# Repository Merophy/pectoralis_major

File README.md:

# pectoralis_major
The pectoralis is a large muscle that attaches to the humerus of the wing at the deltopectoral crest.

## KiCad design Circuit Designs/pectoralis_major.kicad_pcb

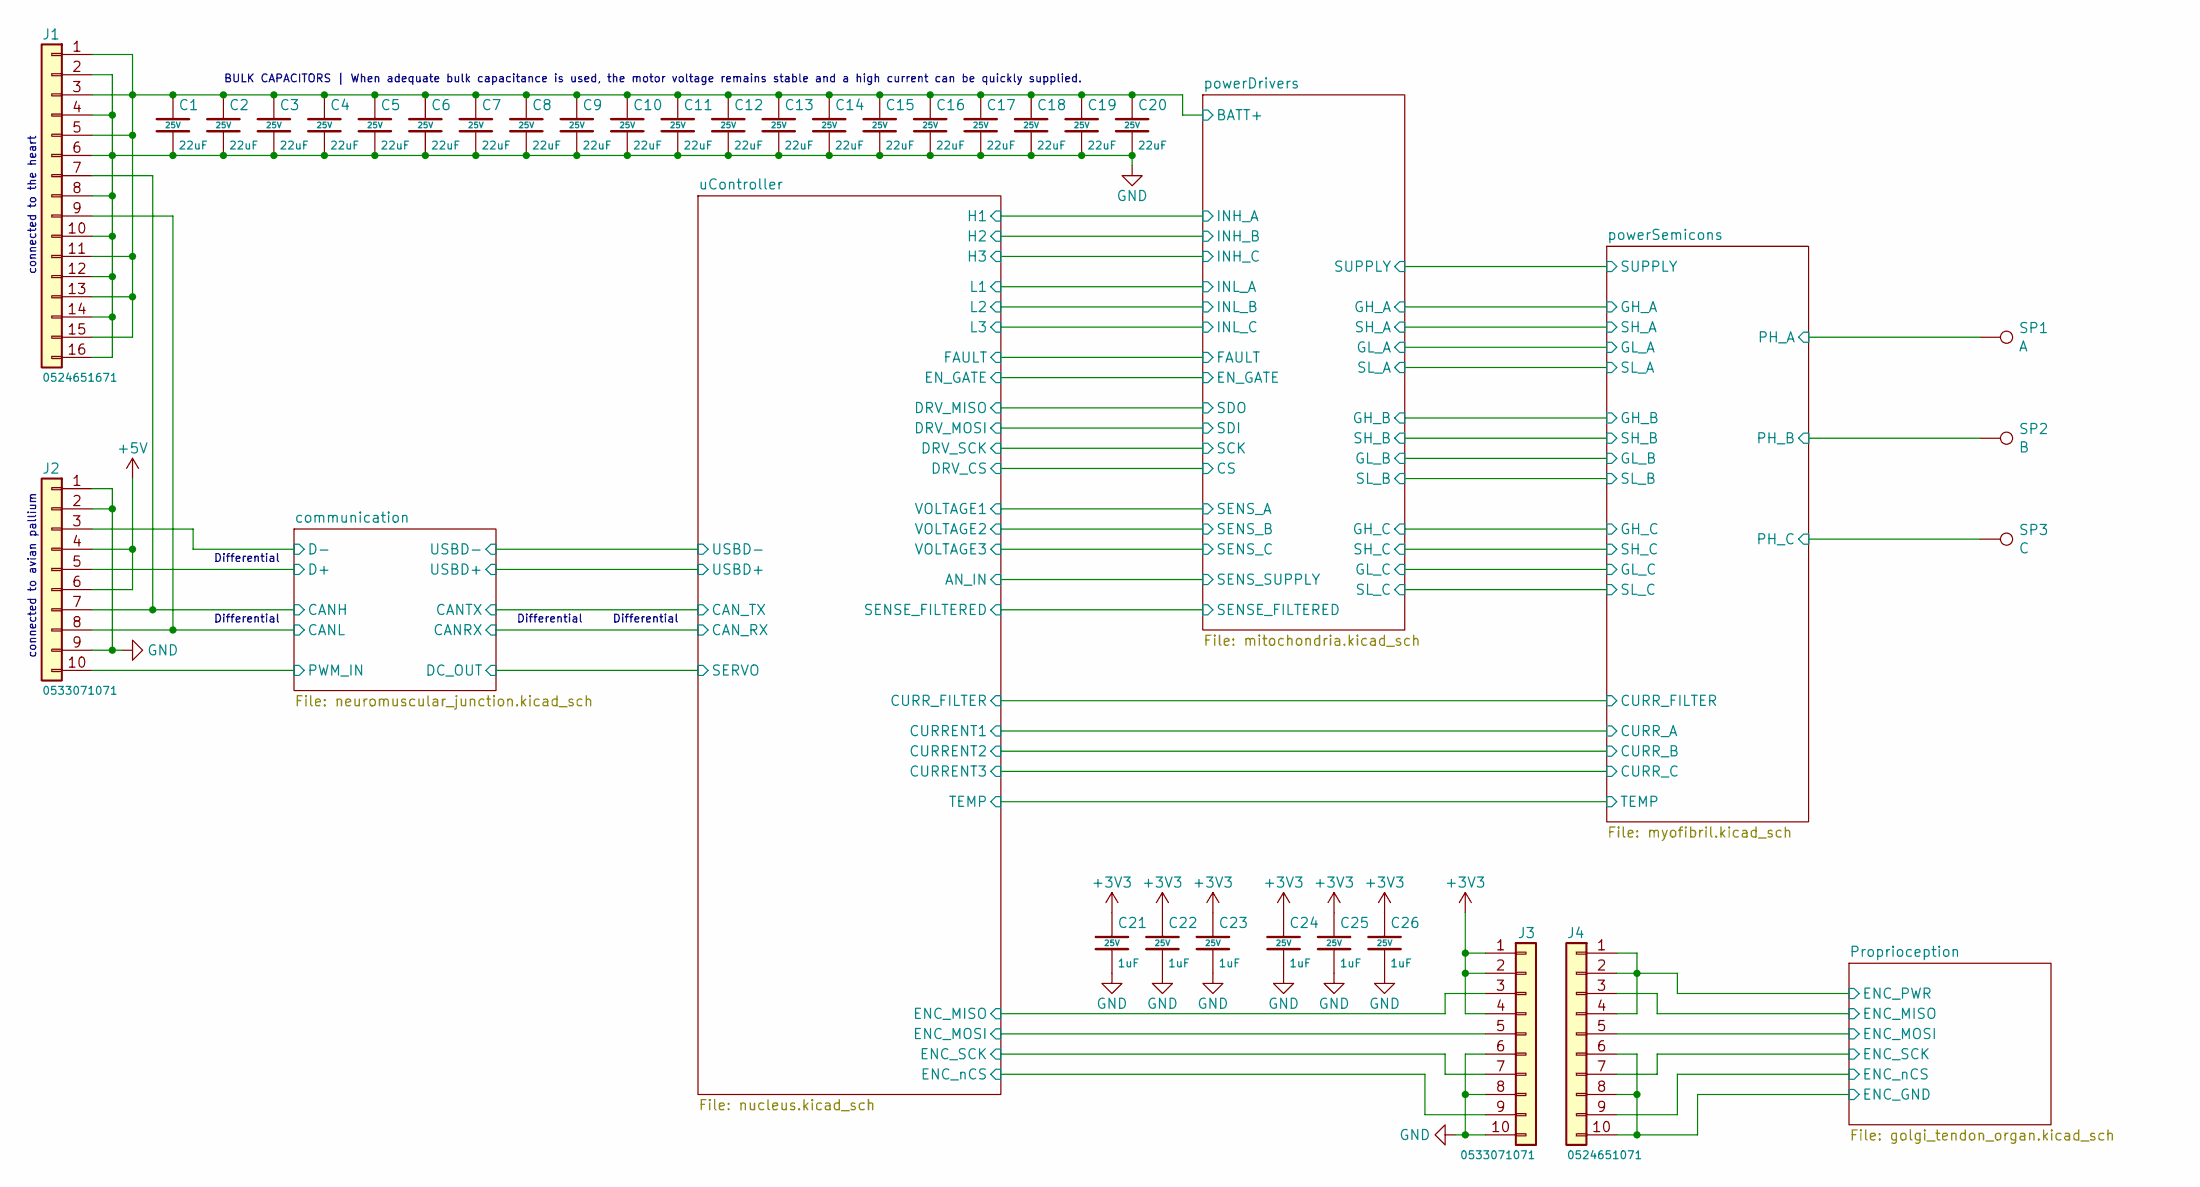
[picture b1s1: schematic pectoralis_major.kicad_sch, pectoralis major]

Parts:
C1, C2, C3, C4, C5, C6, C7, C8, C9, C10, C11, C12, C13, C14, C15, C16, C17, C18, C19, C20: 22uF; C-0805; Voltage 25V; MFR. Part # CL21A226MAQNNNE; JLCPCB Part # C45783
C21, C22, C23, C24, C25, C26: 1uF; C-0402; Voltage 25V; MFR. Part # CL05A105KA5NQNC; JLCPCB Part # C52923
J1: 0524651671; 524651671; MFR Part # 0524651671; Digikey Part # WM7089CT-ND
J2, J3: 0533071071; MFR Part # 0533071071; Digikey Part # WM8918CT-ND
J4: 0524651071; 524651071; MFR Part # 0524651071; Farnell Part # 2063791
SP1: A; SolderPt_2.5x4mm
SP2: B; SolderPt_2.5x4mm
SP3: C; SolderPt_2.5x4mm

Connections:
+3V3: C21.1, C22.1, C23.1, C24.1, C25.1, C26.1, J3.1, J3.2, J3.4; also elsewhere on the board
+5V: J2.4, J2.6; also elsewhere on the board
/Proprioception/ENC_GND: J4.6, J4.8, J4.10; also elsewhere on the board
/Proprioception/ENC_MISO: J4.3; also elsewhere on the board
/Proprioception/ENC_MOSI: J4.5; also elsewhere on the board
/Proprioception/ENC_PWR: J4.1, J4.2, J4.4; also elsewhere on the board
/Proprioception/ENC_SCK: J4.7; also elsewhere on the board
/Proprioception/ENC_nCS: J4.9; also elsewhere on the board
/communication/CANH: J1.7, J2.7; also elsewhere on the board
/communication/CANL: J1.9, J2.8; also elsewhere on the board
/communication/D+: J2.5; also elsewhere on the board
/communication/D-: J2.3; also elsewhere on the board
/communication/PWM_IN: J2.10; also elsewhere on the board
/powerSemicons/PH_A: SP1.1; also elsewhere on the board
/powerSemicons/PH_B: SP2.1; also elsewhere on the board
/powerSemicons/PH_C: SP3.1; also elsewhere on the board
/uController/ENC_MISO: J3.3; also elsewhere on the board
/uController/ENC_MOSI: J3.5; also elsewhere on the board
/uController/ENC_SCK: J3.7; also elsewhere on the board
/uController/ENC_nCS: J3.9; also elsewhere on the board
GND: C1.2, C2.2, C3.2, C4.2, C5.2, C6.2, C7.2, C8.2, C9.2, C10.2, C11.2, C12.2, C13.2, C14.2, C15.2, C16.2, C17.2, C18.2, C19.2, C20.2, C21.2, C22.2, C23.2, C24.2, C25.2, C26.2, J1.2, J1.4, J1.6, J1.8, J1.10, J1.12, J1.14, J1.16, J2.1, J2.2, J2.9, J3.6, J3.8, J3.10; also elsewhere on the board
PVDD2: C1.1, C2.1, C3.1, C4.1, C5.1, C6.1, C7.1, C8.1, C9.1, C10.1, C11.1, C12.1, C13.1, C14.1, C15.1, C16.1, C17.1, C18.1, C19.1, C20.1, J1.1, J1.3, J1.5, J1.11, J1.13, J1.15; also elsewhere on the board

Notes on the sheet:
Differential
BULK CAPACITORS | When adequate bulk capacitance is used, the motor voltage remains stable and a high current can be quickly supplied.
connected to avian pallium
connected to the heart

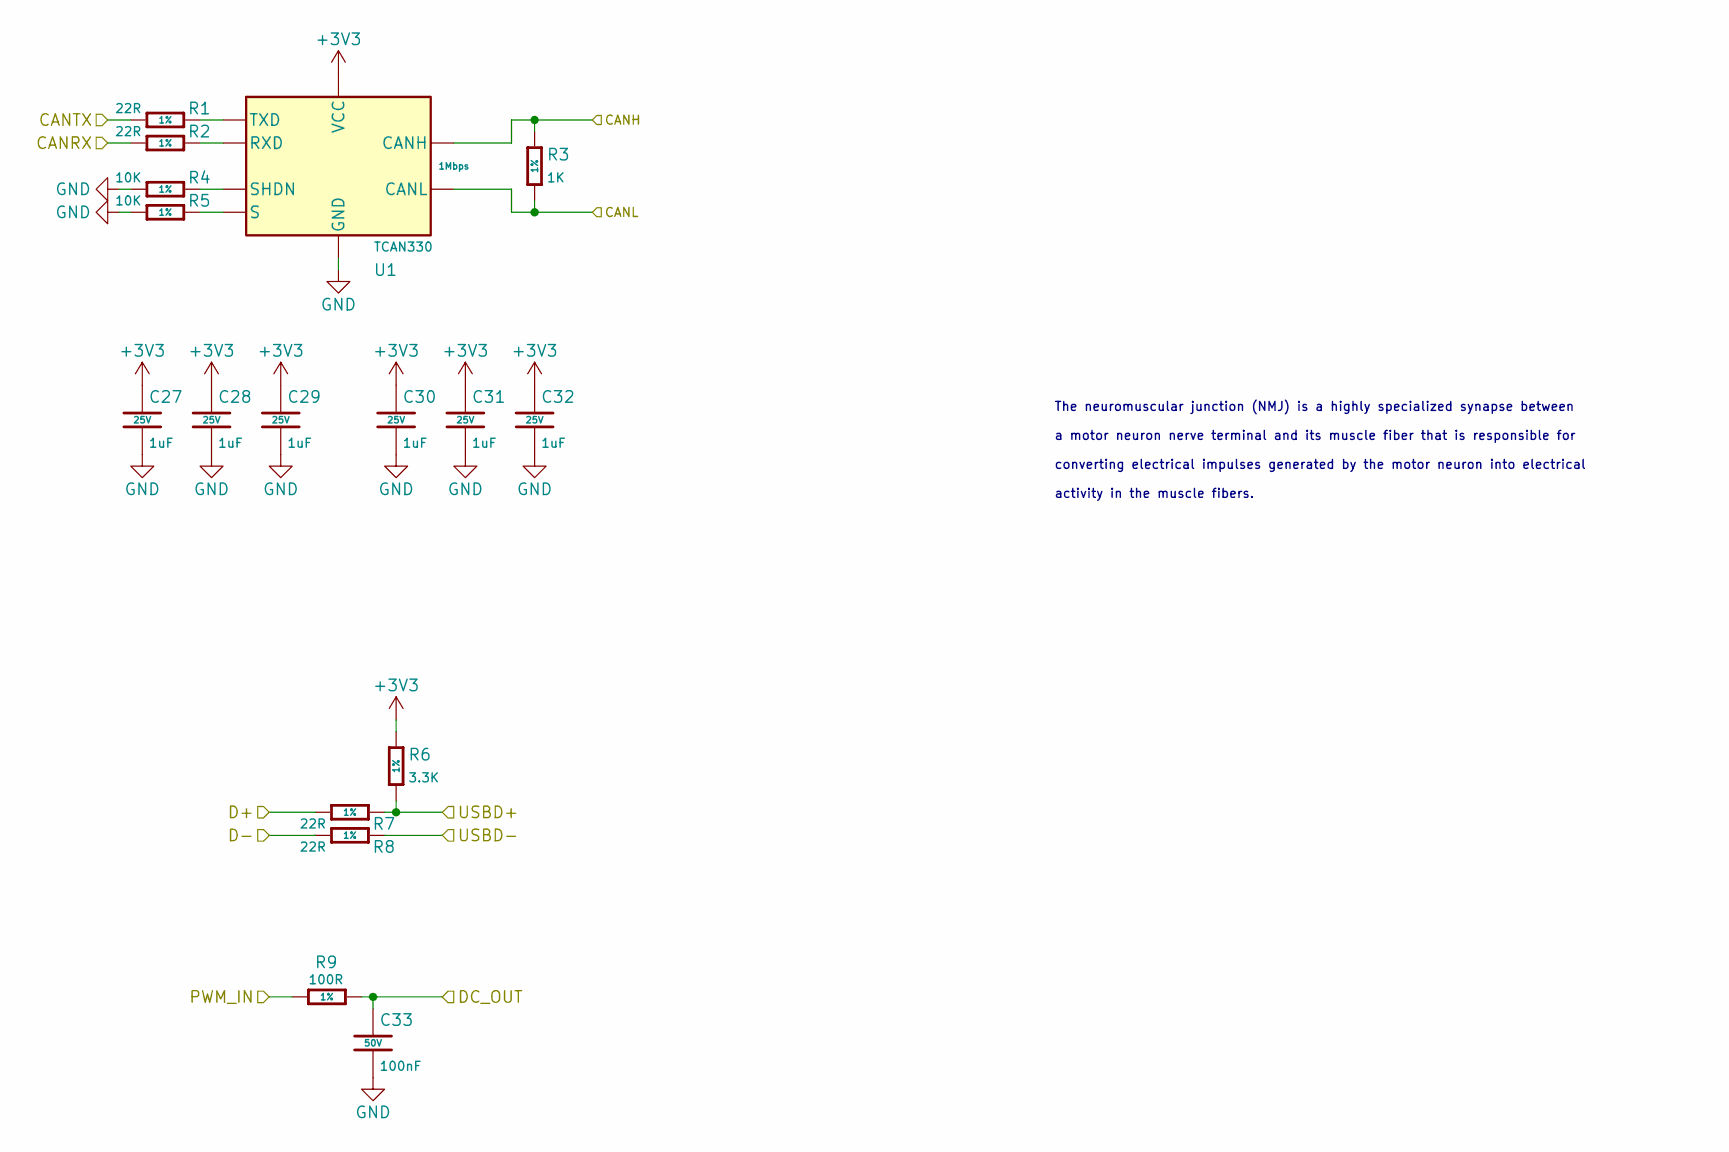
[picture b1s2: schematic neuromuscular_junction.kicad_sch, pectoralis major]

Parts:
C27, C28, C29, C30, C31, C32: 1uF; C-0402; Voltage 25V; MFR. Part # CL05A105KA5NQNC; JLCPCB Part # C52923
C33: 100nF; C-0402; Voltage 50V; MFR. Part # CL05B104KB54PNC; JLCPCB Part # C307331
R1, R2, R7, R8: 22R; R-0402; Tolerance 1%; MFR. Part # 0402WGF220JTCE; JLCPCB Part # C25092
R3: 1K; R-0402; Tolerance 1%; MFR. Part # 0402WGF1001TCE; JLCPCB Part # C11702
R4, R5: 10K; R-0402; Tolerance 1%; MFR. Part # 0402WGF1002TCE; JLCPCB Part # C25744
R6: 3.3K; R-0402; Tolerance 1%; MFR. Part # 0402WGF3301TCE; JLCPCB Part # C25890
R9: 100R; R-0402; Tolerance 1%; MFR. Part # 0402WGF1000TCE; JLCPCB Part # C25076
U1: TCAN330; TSOT-23-8; MFR. Part # TCAN330GDCNR; Digikey Part # 296-TCAN330GDCNRCT-ND

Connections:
+3V3: C27.1, C28.1, C29.1, C30.1, C31.1, C32.1, R6.1, U1.3 (VCC); also elsewhere on the board
/communication/CANH: R3.1, U1.7 (CANH); also elsewhere on the board
/communication/CANL: R3.2, U1.6 (CANL); also elsewhere on the board
/communication/CANRX: R2.1; also elsewhere on the board
/communication/CANTX: R1.1; also elsewhere on the board
/communication/D+: R7.1; also elsewhere on the board
/communication/D-: R8.1; also elsewhere on the board
/communication/DC_OUT: C33.1, R9.2; also elsewhere on the board
/communication/PWM_IN: R9.1; also elsewhere on the board
/communication/USBD+: R6.2, R7.2; also elsewhere on the board
/communication/USBD-: R8.2; also elsewhere on the board
GND: C27.2, C28.2, C29.2, C30.2, C31.2, C32.2, C33.2, R4.1, R5.1, U1.2 (GND); also elsewhere on the board
unnamed: R1.2, U1.1 (TXD)
unnamed: R2.2, U1.4 (RXD)
unnamed: R4.2, U1.5 (SHDN)
unnamed: R5.2, U1.8 (S)

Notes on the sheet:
The neuromuscular junction (NMJ) is a highly specialized synapse between a motor neuron nerve terminal and its muscle fiber that is responsible for converting electrical impulses generated by the motor neuron into electrical activity in the muscle fibers.

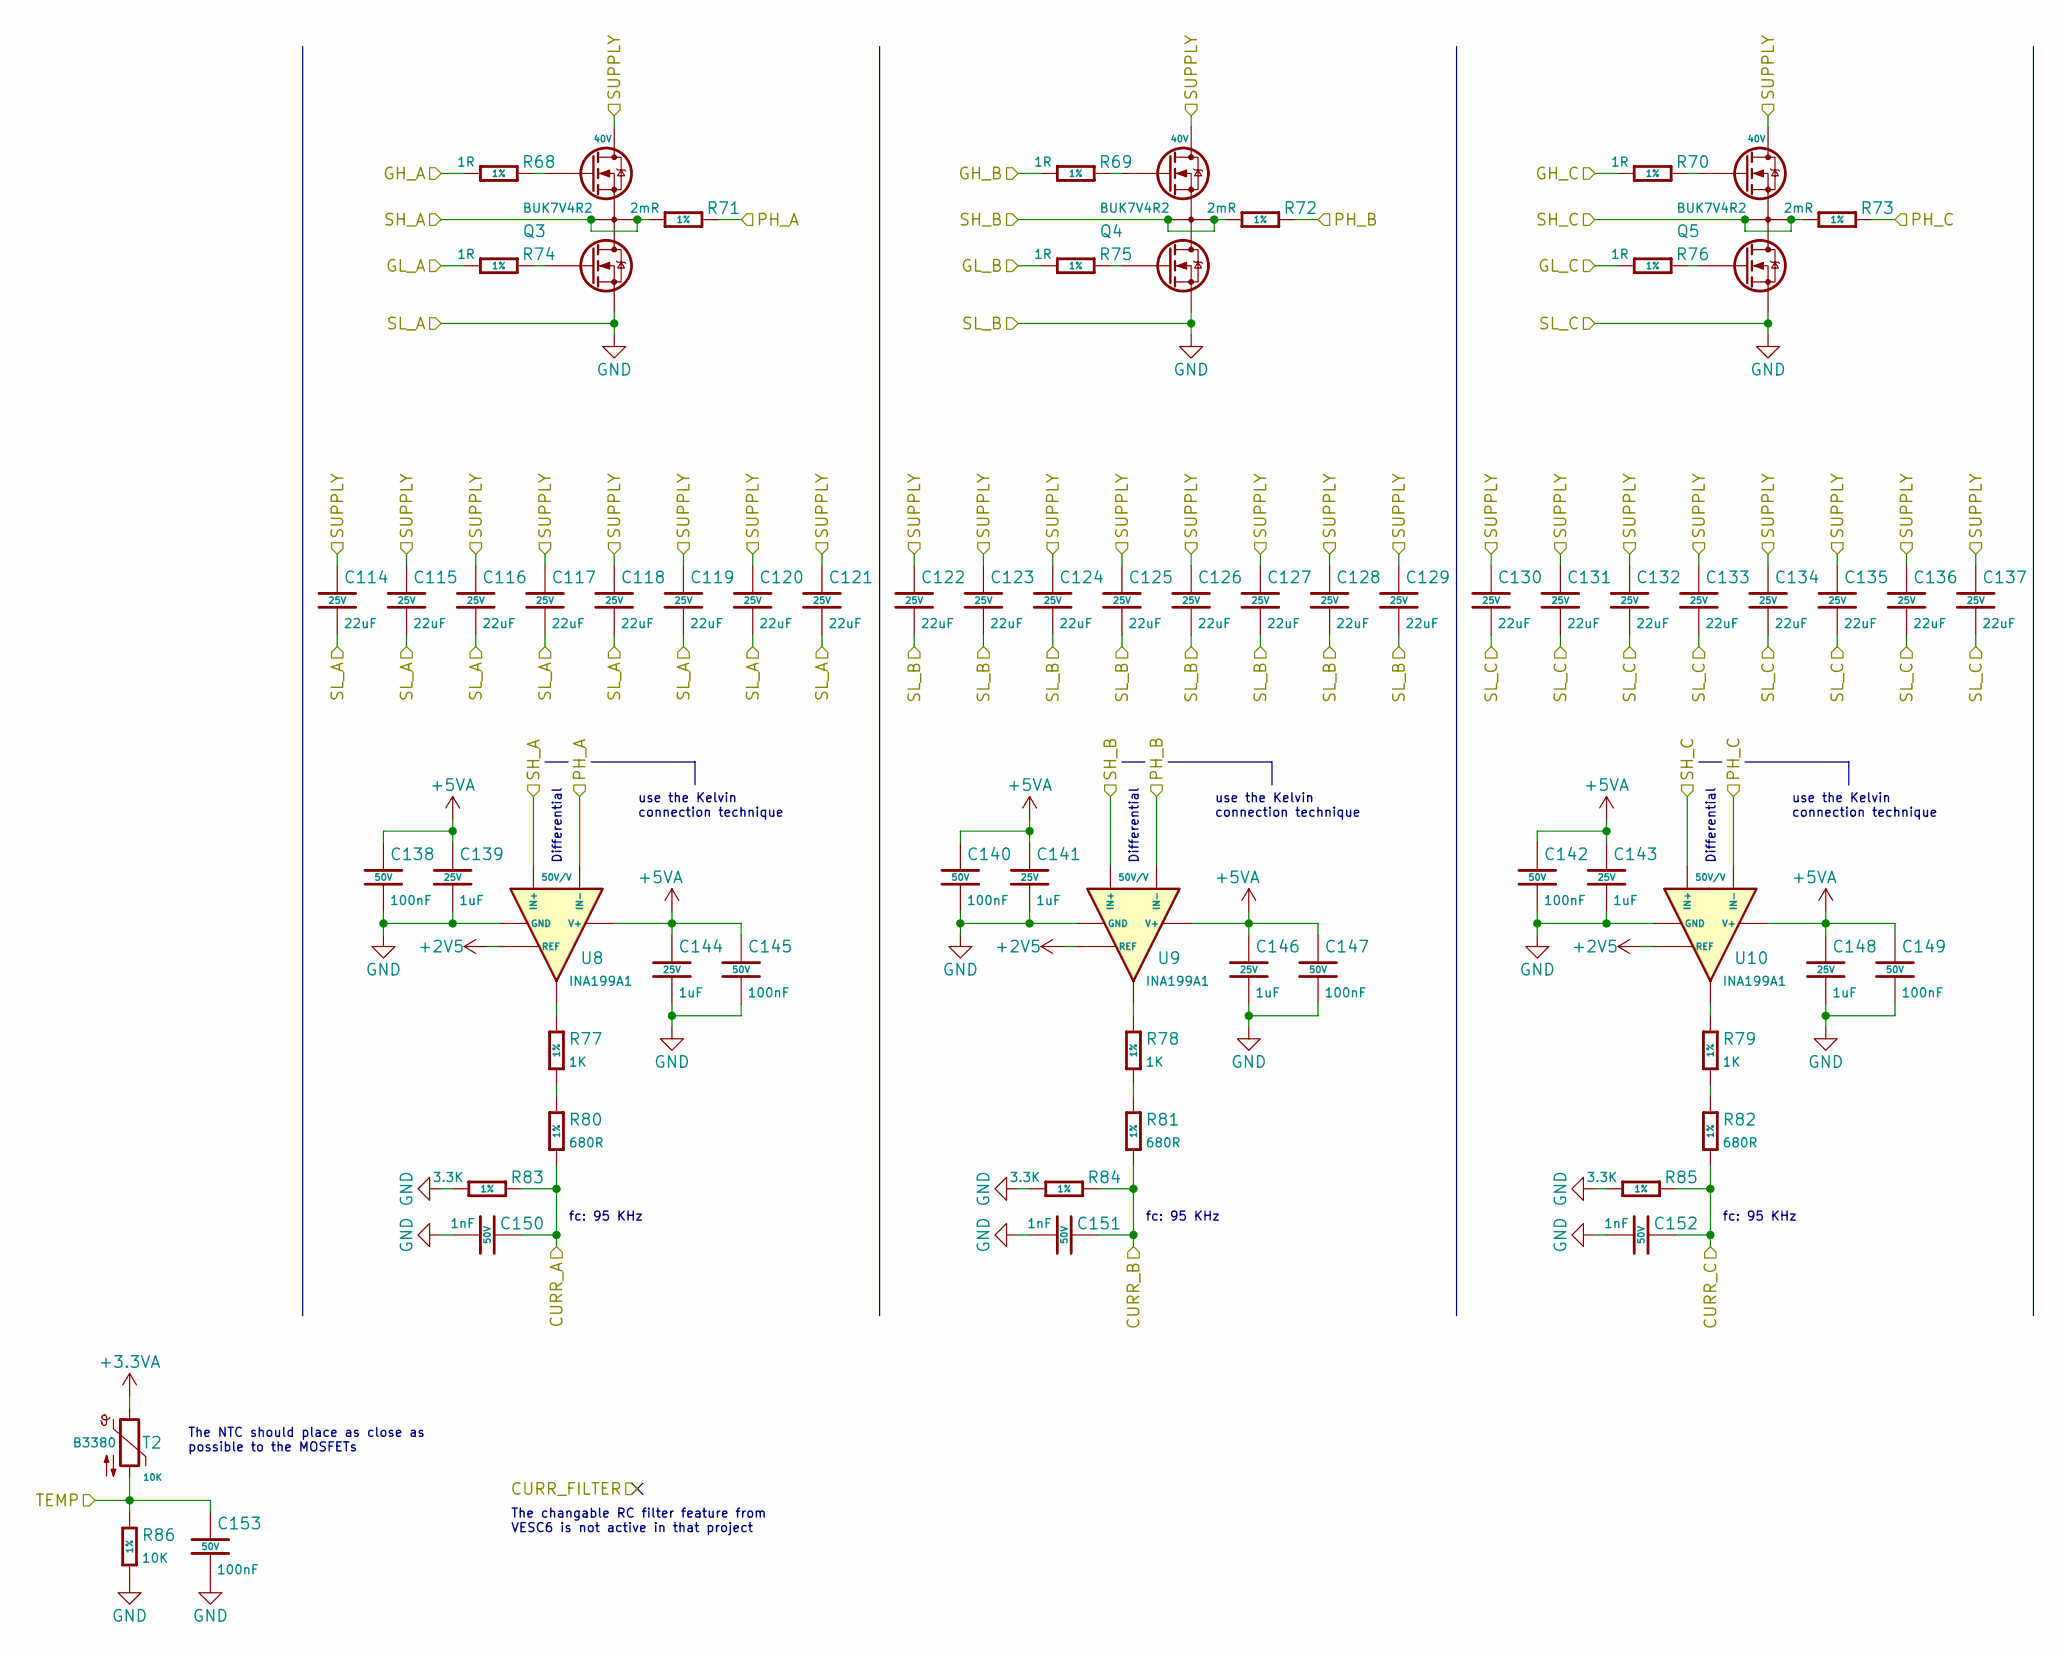
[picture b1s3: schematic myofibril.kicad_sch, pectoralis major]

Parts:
C114, C115, C116, C117, C118, C119, C120, C121, C122, C123, C124, C125, C126, C127, C128, C129, C130, C131, C132, C133, C134, C135, C136, C137: 22uF; C-0805; Voltage 25V; MFR. Part # CL21A226MAQNNNE; JLCPCB Part # C45783
C138, C140, C142, C145, C147, C149, C153: 100nF; C-0402; Voltage 50V; MFR. Part # CL05B104KB54PNC; JLCPCB Part # C307331
C139, C141, C143, C144, C146, C148: 1uF; C-0402; Voltage 25V; MFR. Part # CL05A105KA5NQNC; JLCPCB Part # C52923
C150, C151, C152: 1nF; C-0402; Voltage 50V; MFR. Part # 0402B102K500NT; JLCPCB Part # C1523
Q3, Q4, Q5: BUK7V4R2; SOT-1205; MFR. Part # BUK7V4R2; Digikey Part # 1727-BUK7V4R2-40HXCT-ND
R68, R69, R70, R74, R75, R76: 1R; R-0402; Tolerance 1%; MFR. Part # 0402WGF100KTCE; JLCPCB Part # C25086
R71, R72, R73: 2mR; R-1206; Tolerance 1%; MFR. Part # PA1206FRM470R002L; JLCPCB Part # C728295
R77, R78, R79: 1K; R-0402; Tolerance 1%; MFR. Part # 0402WGF1001TCE; JLCPCB Part # C11702
R80, R81, R82: 680R; R-0402; Tolerance 1%; MFR. Part # 0402WGF6800TCE; JLCPCB Part # C25130
R83, R84, R85: 3.3K; R-0402; Tolerance 1%; MFR. Part # 0402WGF3301TCE; JLCPCB Part # C25890
R86: 10K; R-0402; Tolerance 1%; MFR. Part # 0402WGF1002TCE; JLCPCB Part # C25744
T2: B3380; R-0402; MFR. Part # NCP15XH103F03RC; JLCPCB Part # C77131
U8, U9, U10: INA199A1; SOT-363; MFR. Part # INA199A1DCKR; JLCPCB Part # C59135

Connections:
+2V5: U8.1 (REF), U9.1 (REF), U10.1 (REF); also elsewhere on the board
+3.3VA: T2.1; also elsewhere on the board
+5VA: C138.1, C139.1, C140.1, C141.1, C142.1, C143.1, C144.1, C145.1, C146.1, C147.1, C148.1, C149.1, U8.3 (V+), U9.3 (V+), U10.3 (V+); also elsewhere on the board
/powerDrivers/GH_A: R68.1; also elsewhere on the board
/powerDrivers/GH_B: R69.1; also elsewhere on the board
/powerDrivers/GH_C: R70.1; also elsewhere on the board
/powerDrivers/GL_A: R74.1; also elsewhere on the board
/powerDrivers/GL_B: R75.1; also elsewhere on the board
/powerDrivers/GL_C: R76.1; also elsewhere on the board
/powerDrivers/SH_A: Q3.3 (S1), Q3.6 (S1/D2), R71.1, U8.4 (IN+); also elsewhere on the board
/powerDrivers/SH_B: Q4.3 (S1), Q4.6 (S1/D2), R72.1, U9.4 (IN+); also elsewhere on the board
/powerDrivers/SH_C: Q5.3 (S1), Q5.6 (S1/D2), R73.1, U10.4 (IN+); also elsewhere on the board
/powerSemicons/CURR_A: C150.2, R80.2, R83.2; also elsewhere on the board
/powerSemicons/CURR_B: C151.2, R81.2, R84.2; also elsewhere on the board
/powerSemicons/CURR_C: C152.2, R82.2, R85.2; also elsewhere on the board
/powerSemicons/PH_A: R71.2, U8.5 (IN-); also elsewhere on the board
/powerSemicons/PH_B: R72.2, U9.5 (IN-); also elsewhere on the board
/powerSemicons/PH_C: R73.2, U10.5 (IN-); also elsewhere on the board
/powerSemicons/TEMP: C153.1, R86.1, T2.2; also elsewhere on the board
GND: C114.2, C115.2, C116.2, C117.2, C118.2, C119.2, C120.2, C121.2, C122.2, C123.2, C124.2, C125.2, C126.2, C127.2, C128.2, C129.2, C130.2, C131.2, C132.2, C133.2, C134.2, C135.2, C136.2, C137.2, C138.2, C139.2, C140.2, C141.2, C142.2, C143.2, C144.2, C145.2, C146.2, C147.2, C148.2, C149.2, C150.1, C151.1, C152.1, C153.2, Q3.1 (S2), Q4.1 (S2), Q5.1 (S2), R83.1, R84.1, R85.1, R86.2, U8.2 (GND), U9.2 (GND), U10.2 (GND); also elsewhere on the board
unnamed: Q3.2 (G2), R74.2
unnamed: Q3.4 (G1), R68.2
unnamed: Q4.2 (G2), R75.2
unnamed: Q4.4 (G1), R69.2
unnamed: Q5.2 (G2), R76.2
unnamed: Q5.4 (G1), R70.2
unnamed: R77.1, U8.6
unnamed: R77.2, R80.1
unnamed: R78.1, U9.6
unnamed: R78.2, R81.1
unnamed: R79.1, U10.6
unnamed: R79.2, R82.1
PVDD2: C114.1, C115.1, C116.1, C117.1, C118.1, C119.1, C120.1, C121.1, C122.1, C123.1, C124.1, C125.1, C126.1, C127.1, C128.1, C129.1, C130.1, C131.1, C132.1, C133.1, C134.1, C135.1, C136.1, C137.1, Q3.5 (D1), Q4.5 (D1), Q5.5 (D1); also elsewhere on the board

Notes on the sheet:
Differential
The changable RC filter feature from VESC6 is not active in that project
use the Kelvin connection technique
fc: 95 KHz
The NTC should place as close as possible to the MOSFETs

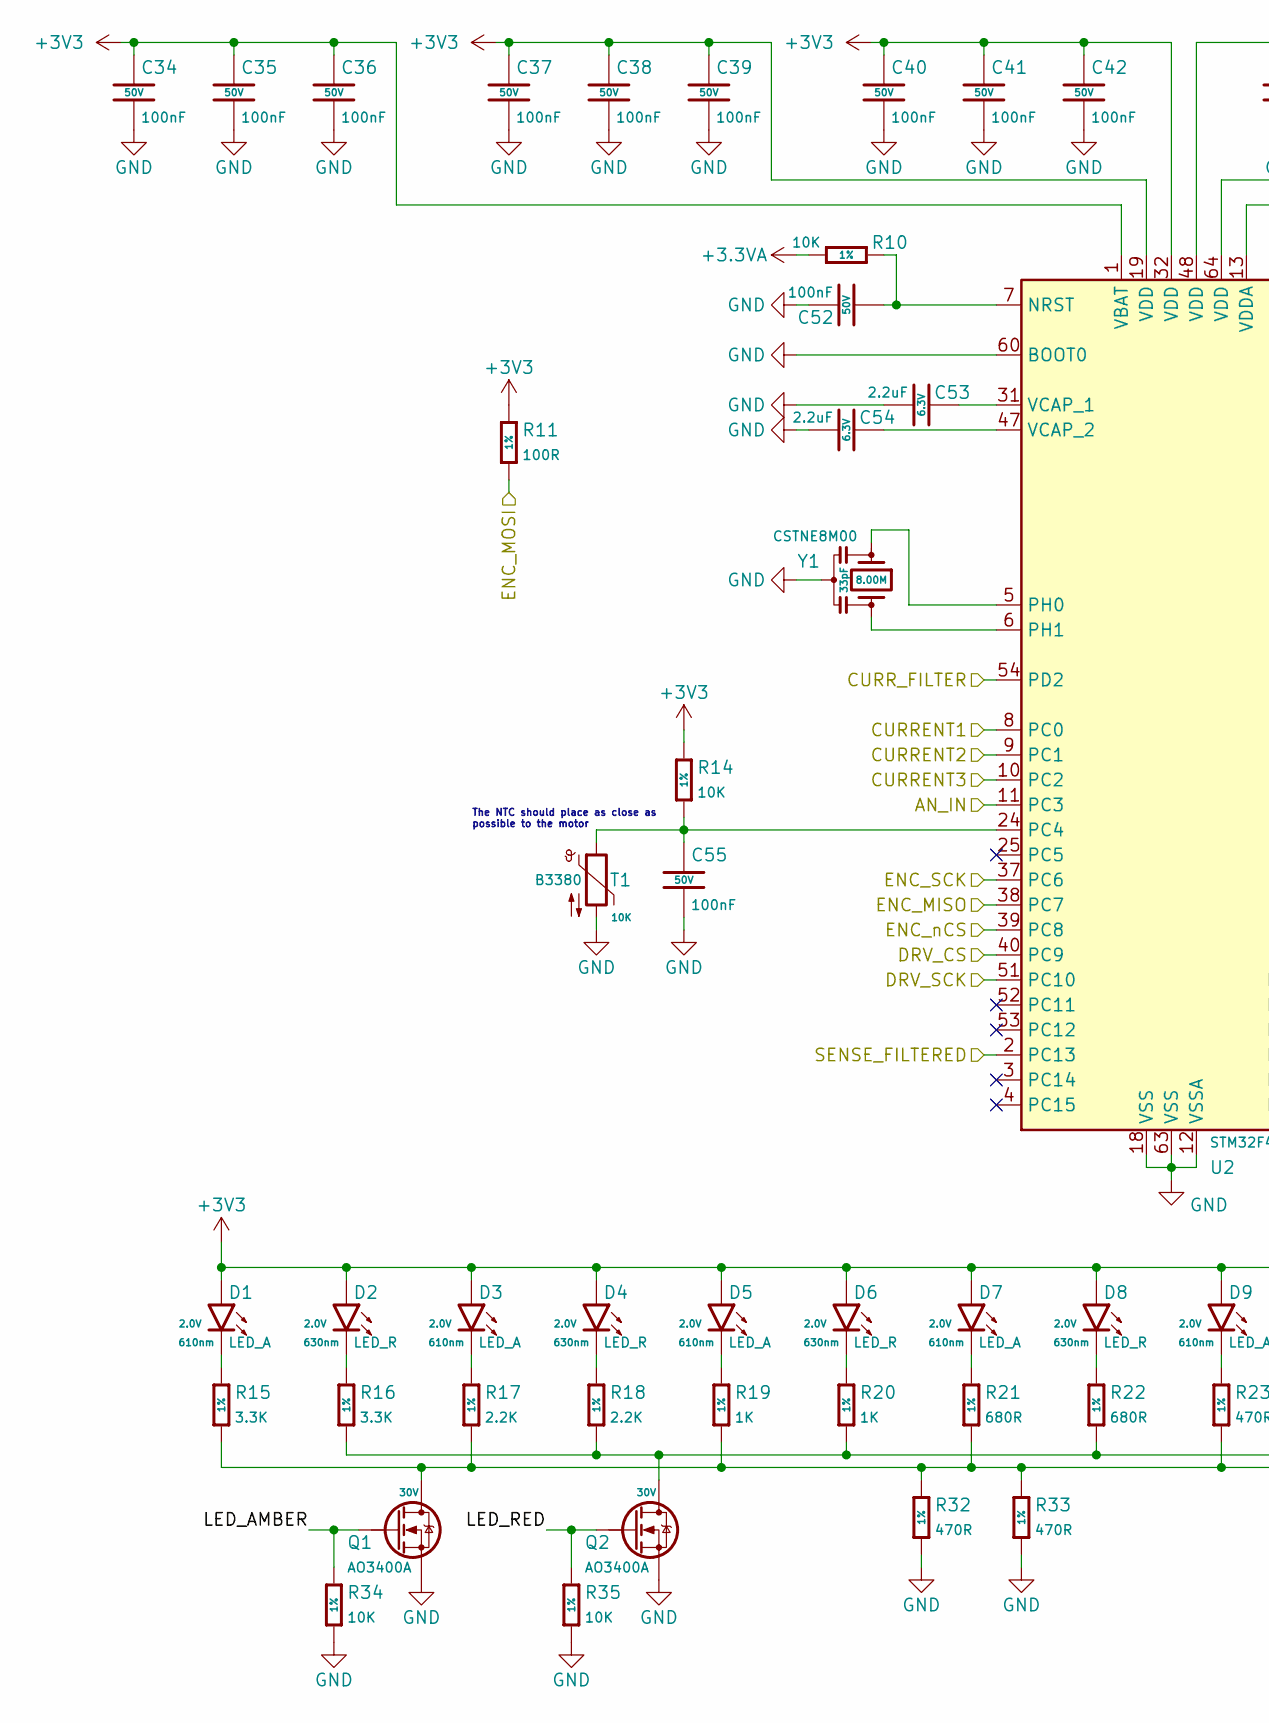
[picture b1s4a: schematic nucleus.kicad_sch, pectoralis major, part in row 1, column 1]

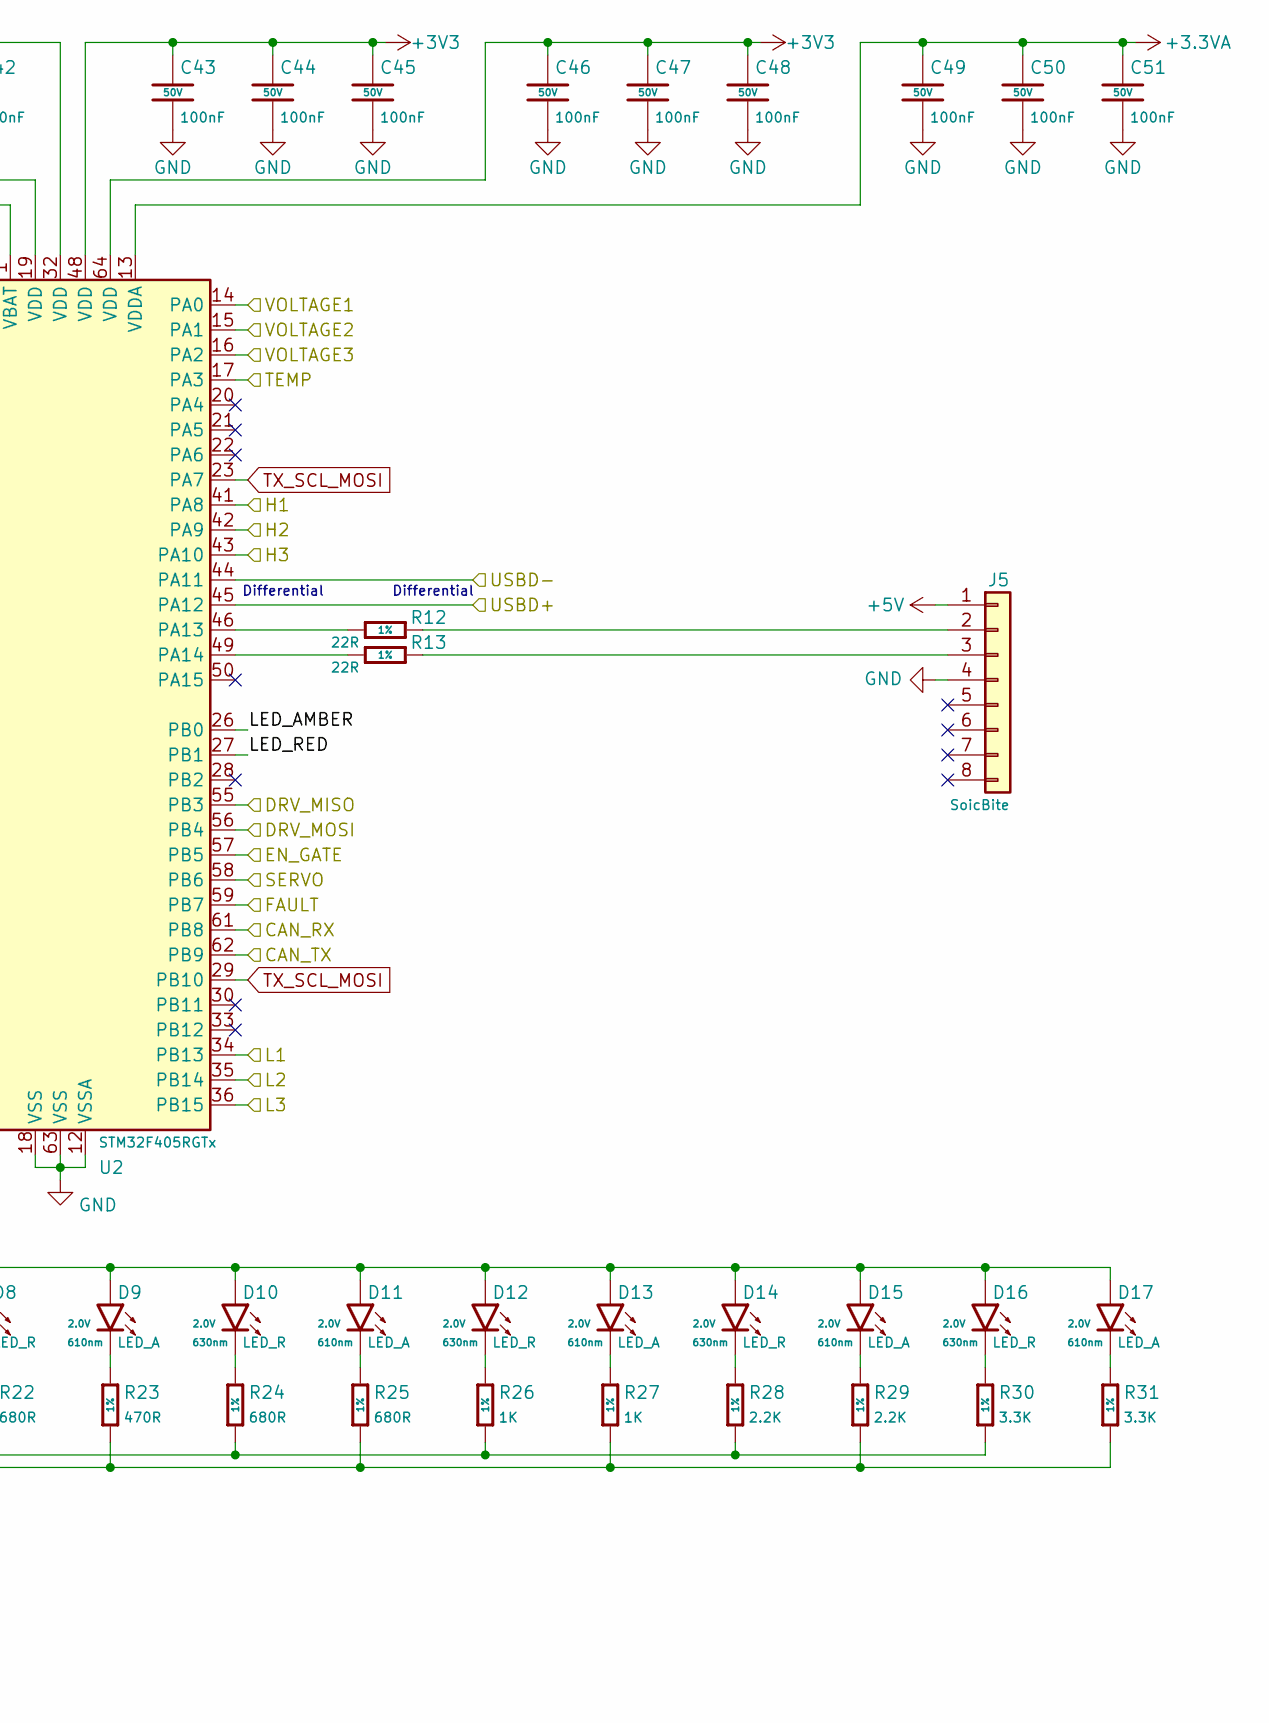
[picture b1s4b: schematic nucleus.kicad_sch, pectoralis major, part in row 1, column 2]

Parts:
C34, C35, C36, C37, C38, C39, C40, C41, C42, C43, C44, C45, C46, C47, C48, C49, C50, C51, C52, C55: 100nF; C-0402; Voltage 50V; MFR. Part # CL05B104KB54PNC; JLCPCB Part # C307331
C53, C54: 2.2uF; C-0402; Voltage 6.3V; MFR. Part # CL05A225MQ5NSNC; JLCPCB Part # C12530
D1, D3, D5, D7, D9, D11, D13, D15, D17: LED_A; LED-0603; MFR. Part # BL-HJC36A-AV-TRB; JLCPCB Part # C138546
D2, D4, D6, D8, D10, D12, D14, D16: LED_R; LED-0603; MFR. Part # KT-0603R; JLCPCB Part # C2286
J5: SoicBite
Q1, Q2: AO3400A; SOT-23; MFR. Part # AO3400A; JLCPCB Part # C20917
R10, R14, R34, R35: 10K; R-0402; Tolerance 1%; MFR. Part # 0402WGF1002TCE; JLCPCB Part # C25744
R11: 100R; R-0402; Tolerance 1%; MFR. Part # 0402WGF1000TCE; JLCPCB Part # C25076
R12, R13: 22R; R-0402; Tolerance 1%; MFR. Part # 0402WGF220JTCE; JLCPCB Part # C25092
R15, R16, R30, R31: 3.3K; R-0402; Tolerance 1%; MFR. Part # 0402WGF3301TCE; JLCPCB Part # C25890
R17, R18, R28, R29: 2.2K; R-0402; Tolerance 1%; MFR. Part # 0402WGF2201TCE; JLCPCB Part # C25879
R19, R20, R26, R27: 1K; R-0402; Tolerance 1%; MFR. Part # 0402WGF1001TCE; JLCPCB Part # C11702
R21, R22, R24, R25: 680R; R-0402; Tolerance 1%; MFR. Part # 0402WGF6800TCE; JLCPCB Part # C25130
R23, R32, R33: 470R; R-0402; Tolerance 1%; MFR. Part # 0402WGF4700TCE; JLCPCB Part # C25117
T1: B3380; R-0402; MFR. Part # NCP15XH103F03RC; JLCPCB Part # C77131
U2: STM32F405RGTx; LQFP-64; MFR. Part # STM32F405RGT6; Digikey Part # 497-11767-ND
Y1: CSTNE8M00; CSTNE; MFR. Part # CSTNE8M00G550000R0; Digikey Part # 490-17958-1-ND

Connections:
+3.3VA: C49.1, C50.1, C51.1, R10.1, U2.13 (VDDA); also elsewhere on the board
+3V3: C34.1, C35.1, C36.1, C37.1, C38.1, C39.1, C40.1, C41.1, C42.1, C43.1, C44.1, C45.1, C46.1, C47.1, C48.1, D1.2 (A), D2.2 (A), D3.2 (A), D4.2 (A), D5.2 (A), D6.2 (A), D7.2 (A), D8.2 (A), D9.2 (A), D10.2 (A), D11.2 (A), D12.2 (A), D13.2 (A), D14.2 (A), D15.2 (A), D16.2 (A), D17.2 (A), R11.1, R14.1, U2.1 (VBAT), U2.19 (VDD), U2.32 (VDD), U2.48 (VDD), U2.64 (VDD); also elsewhere on the board
+5V: J5.1; also elsewhere on the board
/communication/CANRX: U2.61 (PB8); also elsewhere on the board
/communication/CANTX: U2.62 (PB9); also elsewhere on the board
/communication/DC_OUT: U2.58 (PB6); also elsewhere on the board
/communication/USBD+: U2.45 (PA12); also elsewhere on the board
/communication/USBD-: U2.44 (PA11); also elsewhere on the board
/powerDrivers/CS: U2.40 (PC9); also elsewhere on the board
/powerDrivers/EN_GATE: U2.57 (PB5); also elsewhere on the board
/powerDrivers/FAULT: U2.59 (PB7); also elsewhere on the board
/powerDrivers/INH_A: U2.41 (PA8); also elsewhere on the board
/powerDrivers/INH_B: U2.42 (PA9); also elsewhere on the board
/powerDrivers/INH_C: U2.43 (PA10); also elsewhere on the board
/powerDrivers/INL_A: U2.34 (PB13); also elsewhere on the board
/powerDrivers/INL_B: U2.35 (PB14); also elsewhere on the board
/powerDrivers/INL_C: U2.36 (PB15); also elsewhere on the board
/powerDrivers/SCK: U2.51 (PC10); also elsewhere on the board
/powerDrivers/SDI: U2.56 (PB4); also elsewhere on the board
/powerDrivers/SDO: U2.55 (PB3); also elsewhere on the board
/powerDrivers/SENSE_FILTERED: U2.2 (PC13)
/powerDrivers/SENS_A: U2.14 (PA0); also elsewhere on the board
/powerDrivers/SENS_B: U2.15 (PA1); also elsewhere on the board
/powerDrivers/SENS_C: U2.16 (PA2); also elsewhere on the board
/powerDrivers/SENS_SUPPLY: U2.11 (PC3); also elsewhere on the board
/powerSemicons/CURR_A: U2.8 (PC0); also elsewhere on the board
/powerSemicons/CURR_B: U2.9 (PC1); also elsewhere on the board
/powerSemicons/CURR_C: U2.10 (PC2); also elsewhere on the board
/powerSemicons/CURR_FILTER: U2.54 (PD2)
/powerSemicons/TEMP: U2.17 (PA3); also elsewhere on the board
/uController/ENC_MISO: U2.38 (PC7); also elsewhere on the board
/uController/ENC_MOSI: R11.2; also elsewhere on the board
/uController/ENC_SCK: U2.37 (PC6); also elsewhere on the board
/uController/ENC_nCS: U2.39 (PC8); also elsewhere on the board
/uController/LED_AMBER: Q1.1 (G), R34.1, U2.26 (PB0)
/uController/LED_RED: Q2.1 (G), R35.1, U2.27 (PB1)
GND: C34.2, C35.2, C36.2, C37.2, C38.2, C39.2, C40.2, C41.2, C42.2, C43.2, C44.2, C45.2, C46.2, C47.2, C48.2, C49.2, C50.2, C51.2, C52.1, C53.1, C54.1, C55.2, J5.4, Q1.2 (S), Q2.2 (S), R32.2, R33.2, R34.2, R35.2, T1.2, U2.12 (VSSA), U2.18 (VSS), U2.60 (BOOT0), U2.63 (VSS), Y1.2; also elsewhere on the board
unnamed: C52.2, R10.2, U2.7 (NRST)
unnamed: C53.2, U2.31 (VCAP_1)
unnamed: C54.2, U2.47 (VCAP_2)
unnamed: C55.1, R14.2, T1.1, U2.24 (PC4)
unnamed: D1.1 (K), R15.1
unnamed: D2.1 (K), R16.1
unnamed: D3.1 (K), R17.1
unnamed: D4.1 (K), R18.1
unnamed: D5.1 (K), R19.1
unnamed: D6.1 (K), R20.1
unnamed: D7.1 (K), R21.1
unnamed: D8.1 (K), R22.1
unnamed: D9.1 (K), R23.1
unnamed: D10.1 (K), R24.1
unnamed: D11.1 (K), R25.1
unnamed: D12.1 (K), R26.1
unnamed: D13.1 (K), R27.1
unnamed: D14.1 (K), R28.1
unnamed: D15.1 (K), R29.1
unnamed: D16.1 (K), R30.1
unnamed: D17.1 (K), R31.1
unnamed: J5.2, R12.2
unnamed: J5.3, R13.2
unnamed: Q1.3 (D), R15.2, R17.2, R19.2, R21.2, R23.2, R25.2, R27.2, R29.2, R31.2, R32.1, R33.1
unnamed: Q2.3 (D), R16.2, R18.2, R20.2, R22.2, R24.2, R26.2, R28.2, R30.2
unnamed: R12.1, U2.46 (PA13)
unnamed: R13.1, U2.49 (PA14)
unnamed: U2.5 (PH0), Y1.1
unnamed: U2.6 (PH1), Y1.3
TX_SCL_MOSI: U2.23 (PA7), U2.29 (PB10)

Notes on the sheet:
The NTC should place as close as possible to the motor
Differential
